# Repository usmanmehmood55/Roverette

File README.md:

# Roverette
A small robot or "rover" with some sensors, and WiFi.

Components included:
- [ESP32-WROOM32D](https://lcsc.com/product-detail/WIFI-Modules_Espressif-Systems-ESP32-WROOM-32_C82899.html) 
- [DRV8874](https://www.ti.com/lit/ds/symlink/drv8874.pdf)
- [TPS56628](https://www.ti.com/lit/ds/symlink/tps56628.pdf)
- There's more but I'll add those to the readme later

## To Do
- Complete IMU schematic
- Power path circuit for giving power to ESP32 via USB if connected
- Figure out what the motor placement should be
- PCB outline and component placement

View this project on [CADLAB.io](https://cadlab.io/project/23693), and on [GitHub](https://github.com/usmanmehmood55/Roverette).

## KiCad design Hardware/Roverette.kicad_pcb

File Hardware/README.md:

# Hardware
This folder will contain the KiCAD Project, Schematics & Layout and Project Libraries.

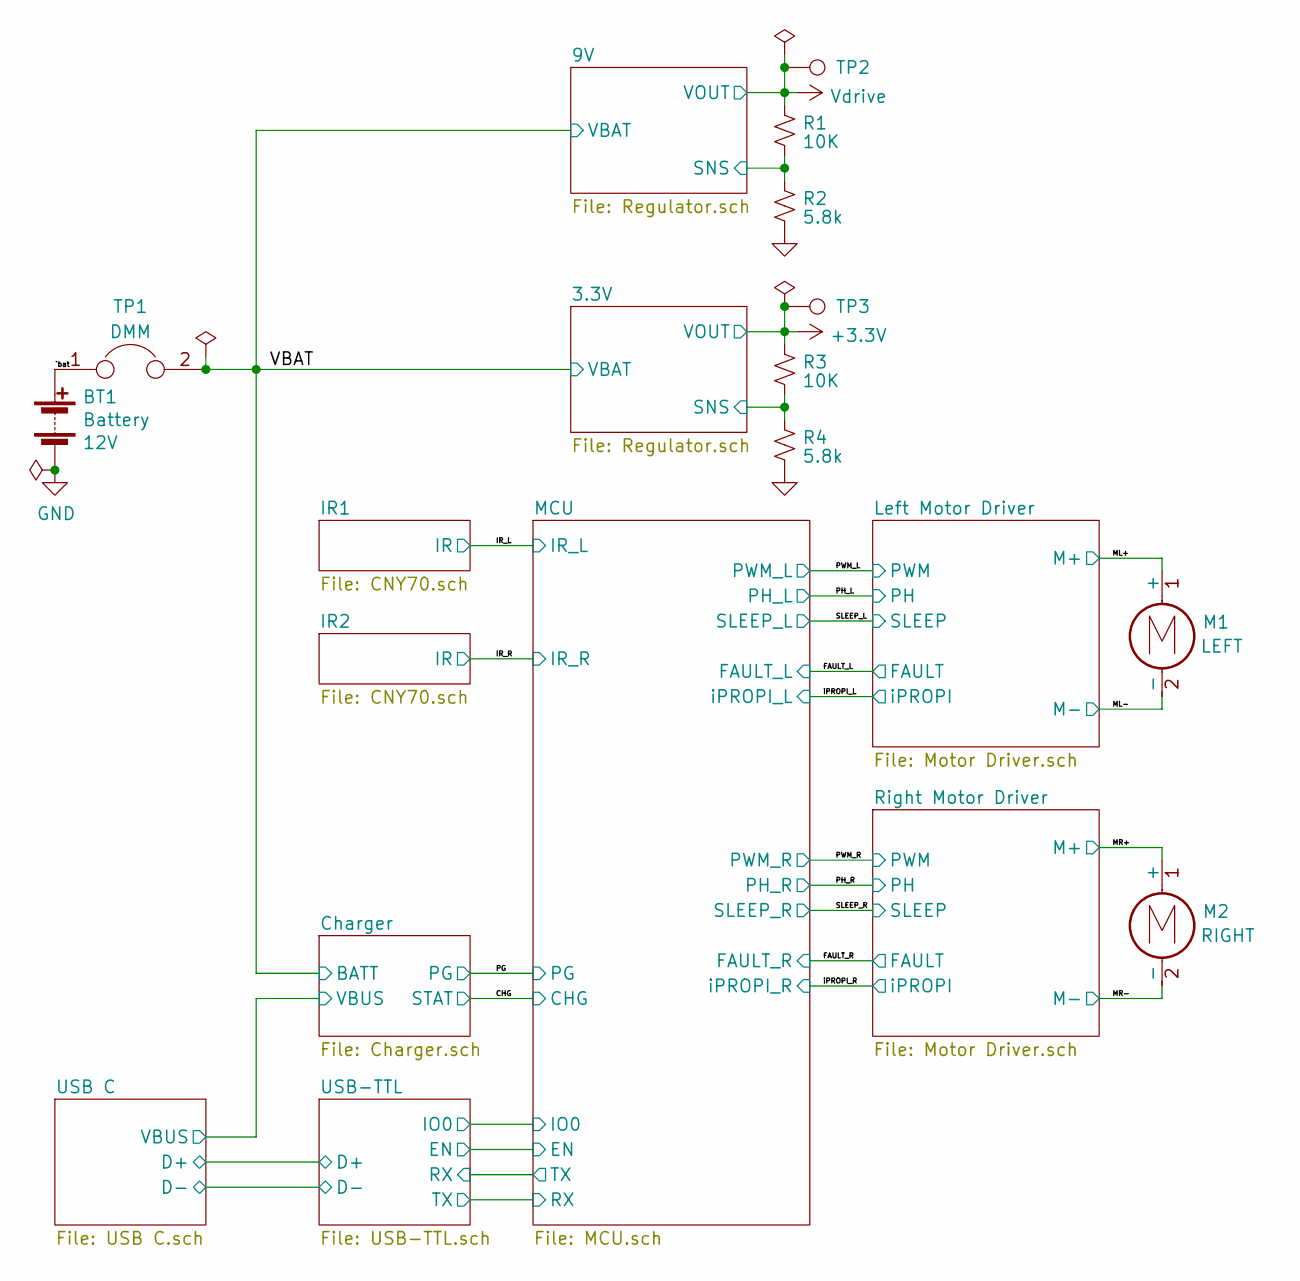
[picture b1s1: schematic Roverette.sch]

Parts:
BT1: Battery; TerminalBlock_bornier-2_P5.08mm
M1, M2: Motor_DC; TerminalBlock_bornier-2_P5.08mm
R1, R3: 10K; R_0805_2012Metric
R2, R4: 5.8k; R_0805_2012Metric
TP1: TestPoint_2Pole; TestPoint_2Pads_Pitch2.54mm_Drill0.8mm
TP2: vDrive; TestPoint_Loop_D1.80mm_Drill1.0mm_Beaded
TP3: 3v3; TestPoint_Loop_D1.80mm_Drill1.0mm_Beaded

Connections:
+3V3: R3.1, TP3.1; also elsewhere on the board
+BATT: TP1.2; also elsewhere on the board
/3.3V/SNS: R3.2, R4.1; also elsewhere on the board
/9V/SNS: R1.2, R2.1; also elsewhere on the board
/ML+: M1.1 (+); also elsewhere on the board
/ML-: M1.2 (-); also elsewhere on the board
/MR+: M2.1 (+); also elsewhere on the board
/MR-: M2.2 (-); also elsewhere on the board
/`bat: BT1.1 (+), TP1.1
GND: BT1.2 (-), R2.2, R4.2; also elsewhere on the board
Vdrive: R1.1, TP2.1; also elsewhere on the board

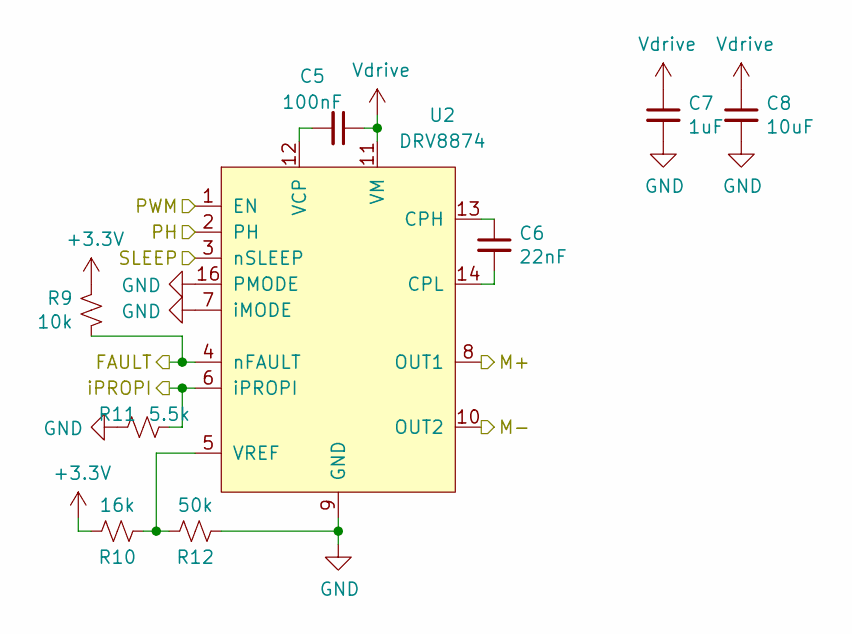
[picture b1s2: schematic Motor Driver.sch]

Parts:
C1: 100nF; C_0805_2012Metric
C2: 22nF; C_0805_2012Metric
C3: 1uF; C_0805_2012Metric
C4: 10uF; C_2220_5650Metric
R5: 10k; R_0805_2012Metric
R6: 16k; R_0805_2012Metric
R7: 5.5k; R_0805_2012Metric
R8: 50k; R_0805_2012Metric
U1: DRV8874; HTSSOP-16-1EP_4.4x5mm_P0.65mm_EP3.4x5mm_Mask3x3mm_ThermalVi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

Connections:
+3V3: R5.1, R6.2; also elsewhere on the board
/FAULT_L: R5.2, U1.4 (nFAULT); also elsewhere on the board
/ML+: U1.8 (OUT1); also elsewhere on the board
/ML-: U1.10 (OUT2); also elsewhere on the board
/PH_L: U1.2 (PH); also elsewhere on the board
/PWM_L: U1.1 (EN); also elsewhere on the board
/SLEEP_L: U1.3 (nSLEEP); also elsewhere on the board
/iPROPI_L: R7.1, U1.6 (iPROPI); also elsewhere on the board
GND: C3.2, C4.2, R7.2, R8.1, U1.7 (iMODE), U1.9 (GND), U1.15 (GND), U1.16 (PMODE), U1.17 (GND); also elsewhere on the board
unnamed: C1.2, U1.12 (VCP)
unnamed: C2.1, U1.13 (CPH)
unnamed: C2.2, U1.14 (CPL)
unnamed: R6.1, R8.2, U1.5 (VREF)
Vdrive: C1.1, C3.1, C4.1, U1.11 (VM); also elsewhere on the board

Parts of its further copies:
C5: 100nF; C_0805_2012Metric
C6: 22nF; C_0805_2012Metric
C7: 1uF; C_0805_2012Metric
C8: 10uF; C_2220_5650Metric
R9: 10k; R_0805_2012Metric
R10: 16k; R_0805_2012Metric
R11: 5.5k; R_0805_2012Metric
R12: 50k; R_0805_2012Metric
U2: DRV8874; HTSSOP-16-1EP_4.4x5mm_P0.65mm_EP3.4x5mm_Mask3x3mm_ThermalVi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

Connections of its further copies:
+3V3: R9.1, R10.2; also elsewhere on the board
/FAULT_R: R9.2, U2.4 (nFAULT); also elsewhere on the board
/MR+: U2.8 (OUT1); also elsewhere on the board
/MR-: U2.10 (OUT2); also elsewhere on the board
/PH_R: U2.2 (PH); also elsewhere on the board
/PWM_R: U2.1 (EN); also elsewhere on the board
/SLEEP_R: U2.3 (nSLEEP); also elsewhere on the board
/iPROPI_R: R11.1, U2.6 (iPROPI); also elsewhere on the board
GND: C7.2, C8.2, R11.2, R12.1, U2.7 (iMODE), U2.9 (GND), U2.15 (GND), U2.16 (PMODE), U2.17 (GND); also elsewhere on the board
unnamed: C5.2, U2.12 (VCP)
unnamed: C6.1, U2.13 (CPH)
unnamed: C6.2, U2.14 (CPL)
unnamed: R10.1, R12.2, U2.5 (VREF)
Vdrive: C5.1, C7.1, C8.1, U2.11 (VM); also elsewhere on the board

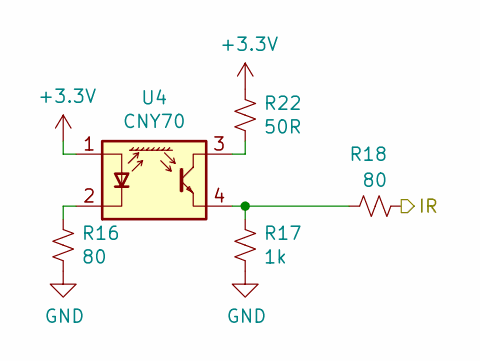
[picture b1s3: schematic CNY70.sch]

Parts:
R13, R15: 80; R_0805_2012Metric
R14: 1k; R_0805_2012Metric
R21: 50R; R_0805_2012Metric
U3: CNY70; Vishay_CNY70

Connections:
+3V3: R21.1, U3.1 (A); also elsewhere on the board
/IR_L: R15.2; also elsewhere on the board
GND: R13.2, R14.2; also elsewhere on the board
unnamed: R13.1, U3.2 (K)
unnamed: R14.1, R15.1, U3.4 (E)
unnamed: R21.2, U3.3 (C)

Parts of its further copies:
R16, R18: 80; R_0805_2012Metric
R17: 1k; R_0805_2012Metric
R22: 50R; R_0805_2012Metric
U4: CNY70; Vishay_CNY70

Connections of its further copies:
+3V3: R22.1, U4.1 (A); also elsewhere on the board
/IR_R: R18.2; also elsewhere on the board
GND: R16.2, R17.2; also elsewhere on the board
unnamed: R16.1, U4.2 (K)
unnamed: R17.1, R18.1, U4.4 (E)
unnamed: R22.2, U4.3 (C)

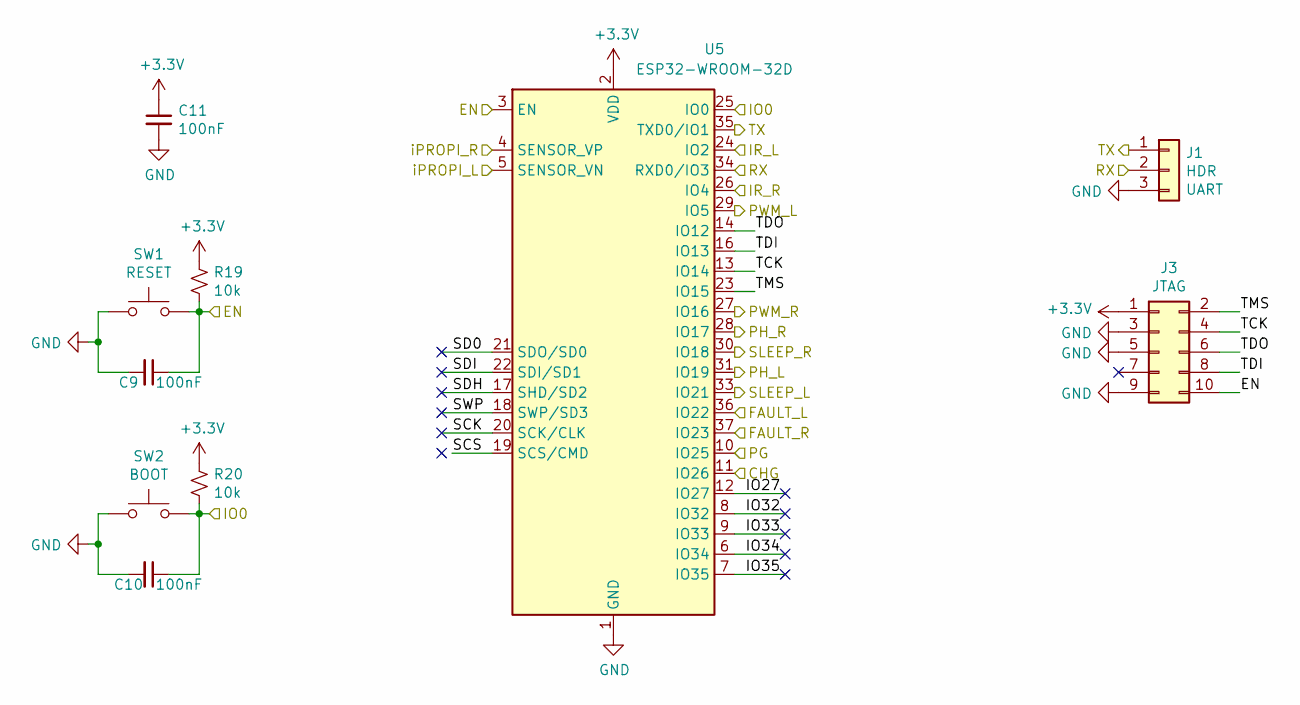
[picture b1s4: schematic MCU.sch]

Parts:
C9, C10, C11: 100nF; C_0805_2012Metric
J1: HDR; PinHeader_1x03_P2.54mm_Vertical
J3: JTAG; PinHeader_2x05_P1.27mm_Vertical_SMD
R19, R20: 10k; R_0805_2012Metric
SW1, SW2: SW_Push; SW_SPST_CK_RS282G05A3
U5: ESP32-WROOM-32D; ESP32-WROOM-32

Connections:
+3V3: C11.1, J3.1, R19.1, R20.1, U5.2 (VDD); also elsewhere on the board
/CHG: U5.11 (IO26); also elsewhere on the board
/FAULT_L: U5.36 (IO22); also elsewhere on the board
/FAULT_R: U5.37 (IO23); also elsewhere on the board
/IR_L: U5.24 (IO2); also elsewhere on the board
/IR_R: U5.26 (IO4); also elsewhere on the board
/MCU/EN: C9.1, J3.10, R19.2, SW1.2, U5.3 (EN); also elsewhere on the board
/MCU/IO0: C10.1, R20.2, SW2.2, U5.25 (IO0); also elsewhere on the board
/MCU/IO27: U5.12 (IO27)
/MCU/IO32: U5.8 (IO32)
/MCU/IO33: U5.9 (IO33)
/MCU/IO34: U5.6 (IO34)
/MCU/IO35: U5.7 (IO35)
/MCU/RX: J1.2, U5.34 (RXD0/IO3); also elsewhere on the board
/MCU/SCK: U5.20 (SCK/CLK)
/MCU/SCS: U5.19 (SCS/CMD)
/MCU/SD0: U5.21 (SDO/SD0)
/MCU/SDH: U5.17 (SHD/SD2)
/MCU/SDI: U5.22 (SDI/SD1)
/MCU/SWP: U5.18 (SWP/SD3)
/MCU/TCK: J3.4, U5.13 (IO14)
/MCU/TDI: J3.8, U5.16 (IO13)
/MCU/TDO: J3.6, U5.14 (IO12)
/MCU/TMS: J3.2, U5.23 (IO15)
/PG: U5.10 (IO25); also elsewhere on the board
/PH_L: U5.31 (IO19); also elsewhere on the board
/PH_R: U5.28 (IO17); also elsewhere on the board
/PWM_L: U5.29 (IO5); also elsewhere on the board
/PWM_R: U5.27 (IO16); also elsewhere on the board
/SLEEP_L: U5.33 (IO21); also elsewhere on the board
/SLEEP_R: U5.30 (IO18); also elsewhere on the board
/USB-TTL/RX: J1.1, U5.35 (TXD0/IO1); also elsewhere on the board
/iPROPI_L: U5.5 (SENSOR_VN); also elsewhere on the board
/iPROPI_R: U5.4 (SENSOR_VP); also elsewhere on the board
GND: C9.2, C10.2, C11.2, J1.3, J3.3, J3.5, J3.9, SW1.1, SW2.1, U5.1 (GND), U5.15 (GND), U5.38 (GND), U5.39 (GND); also elsewhere on the board

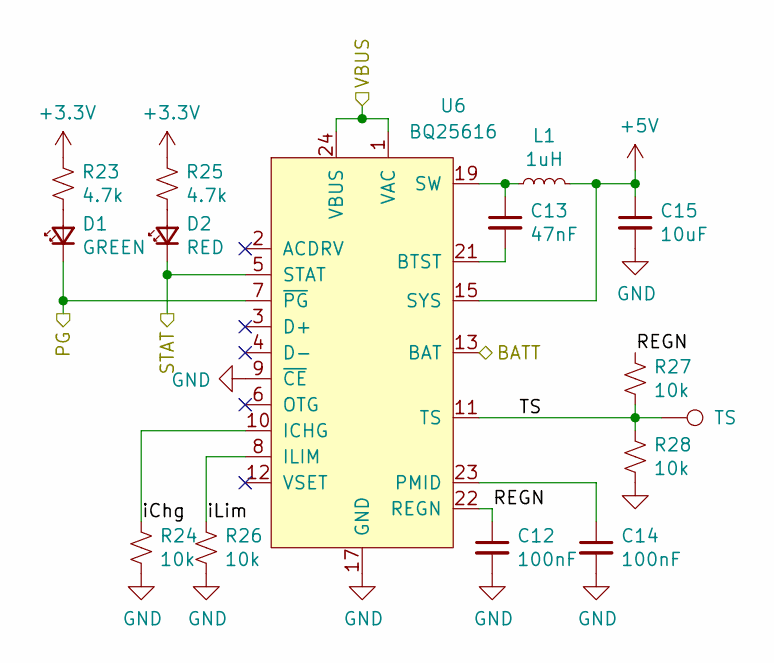
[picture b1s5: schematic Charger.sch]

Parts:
C12, C14: 100nF; C_0805_2012Metric
C13: 47nF; C_0805_2012Metric
C15: 10uF; C_0805_2012Metric
D1: GREEN; LED_0402_1005Metric
D2: RED; LED_0402_1005Metric
L1: 1uH; L_1210_3225Metric; MPN NLCV32T-1R0M-PF
R23, R25: 4.7k; R_0805_2012Metric
R24, R26, R27, R28: 10k; R_0805_2012Metric
TP4: TS; TestPoint_Pad_1.0x1.0mm
U6: BQ25616; WQFN-24-1EP_4x4mm_P0.5mm_EP2.6x2.6mm_ThermalVias

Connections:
+3V3: R23.1, R25.1; also elsewhere on the board
+5V: C15.1, L1.2, U6.15 (SYS), U6.16 (SYS)
+BATT: U6.13 (BAT), U6.14 (BAT); also elsewhere on the board
/CHG: D2.1 (K), U6.5 (STAT); also elsewhere on the board
/Charger/REGN: C12.1, R27.1, U6.22 (REGN)
/Charger/TS: R27.2, R28.1, TP4.1, U6.11 (TS)
/Charger/VBUS: U6.1 (VAC), U6.24 (VBUS); also elsewhere on the board
/Charger/iChg: R24.1, U6.10 (ICHG)
/Charger/iLim: R26.1, U6.8 (ILIM)
/PG: D1.1 (K), U6.7 (~PG); also elsewhere on the board
GND: C12.2, C14.2, C15.2, R24.2, R26.2, R28.2, U6.9 (~CE), U6.17 (GND), U6.18 (GND), U6.25 (GND); also elsewhere on the board
unnamed: C13.1, L1.1, U6.19 (SW), U6.20 (SW)
unnamed: C13.2, U6.21 (BTST)
unnamed: C14.1, U6.23 (PMID)
unnamed: D1.2 (A), R23.2
unnamed: D2.2 (A), R25.2

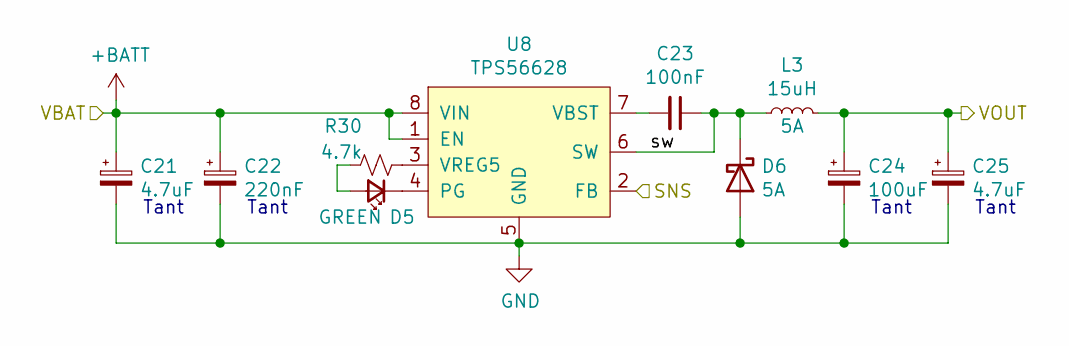
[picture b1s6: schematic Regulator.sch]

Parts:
C16, C20: 4.7uF; CP_EIA-3528-15_AVX-H
C17: 220nF; CP_EIA-3216-18_Kemet-A
C18: 100nF; C_0805_2012Metric
C19: 100uF; CP_EIA-7343-31_Kemet-D
D3: GREEN; LED_0805_2012Metric
D4: 5A; D_SOD-123F
L2: 15uH; L_Neosid_SMs42
R29: 4.7k; R_0805_2012Metric
U7: TPS56628; HSOP-8-1EP_3.9x4.9mm_P1.27mm_EP2.41x3.1mm_ThermalVias

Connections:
+3V3: C19.1, C20.1, L2.2; also elsewhere on the board
+BATT: C16.1, C17.1, U7.1 (EN), U7.8 (VIN); also elsewhere on the board
/3.3V/SNS: U7.2 (FB); also elsewhere on the board
/3.3V/sw: C18.1, D4.1 (K), L2.1, U7.6 (SW)
GND: C16.2, C17.2, C19.2, C20.2, D4.2 (A), U7.5 (GND), U7.9 (GND); also elsewhere on the board
unnamed: C18.2, U7.7 (VBST)
unnamed: D3.1 (K), U7.4 (PG)
unnamed: D3.2 (A), R29.1
unnamed: R29.2, U7.3 (VREG5)

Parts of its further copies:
C21, C25: 4.7uF; CP_EIA-3528-15_AVX-H
C22: 220nF; CP_EIA-3216-18_Kemet-A
C23: 100nF; C_0805_2012Metric
C24: 100uF; CP_EIA-7343-31_Kemet-D
D5: GREEN; LED_0805_2012Metric
D6: 5A; D_SOD-123F
L3: 15uH; L_Neosid_SMs42
R30: 4.7k; R_0805_2012Metric
U8: TPS56628; HSOP-8-1EP_3.9x4.9mm_P1.27mm_EP2.41x3.1mm_ThermalVias

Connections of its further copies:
+BATT: C21.1, C22.1, U8.1 (EN), U8.8 (VIN); also elsewhere on the board
/9V/SNS: U8.2 (FB); also elsewhere on the board
/9V/sw: C23.1, D6.1 (K), L3.1, U8.6 (SW)
GND: C21.2, C22.2, C24.2, C25.2, D6.2 (A), U8.5 (GND), U8.9 (GND); also elsewhere on the board
unnamed: C23.2, U8.7 (VBST)
unnamed: D5.1 (K), U8.4 (PG)
unnamed: D5.2 (A), R30.1
unnamed: R30.2, U8.3 (VREG5)
Vdrive: C24.1, C25.1, L3.2; also elsewhere on the board

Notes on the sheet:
Tant

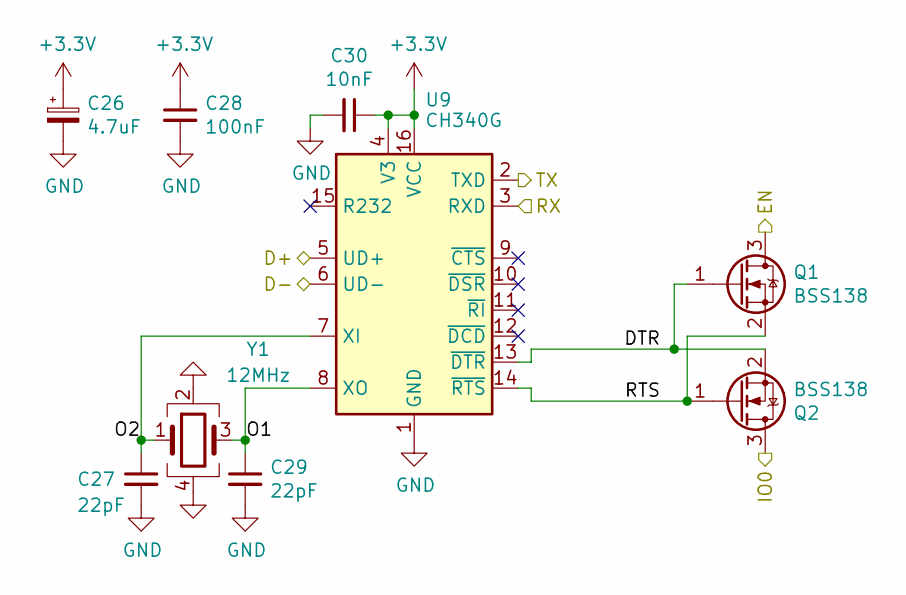
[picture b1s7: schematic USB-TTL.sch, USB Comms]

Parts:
C26: 4.7uF; CP_EIA-3528-15_AVX-H
C27, C29: 22pF; C_0805_2012Metric
C28: 100nF; C_0805_2012Metric
C30: 10nF; C_0805_2012Metric
Q1, Q2: BSS138; SOT-23
U9: CH340G; SOIC-16_3.9x9.9mm_P1.27mm
Y1: 12MHz; Crystal_SMD_3225-4Pin_3.2x2.5mm

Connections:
+3V3: C26.1, C28.1, C30.1, U9.4 (V3), U9.16 (VCC); also elsewhere on the board
/MCU/EN: Q1.3 (D); also elsewhere on the board
/MCU/IO0: Q2.3 (D); also elsewhere on the board
/MCU/RX: U9.2 (TXD); also elsewhere on the board
/USB C/D+: U9.5 (UD+); also elsewhere on the board
/USB C/D-: U9.6 (UD-); also elsewhere on the board
/USB-TTL/DTR: Q1.1 (G), Q2.2 (S), U9.13 (~DTR)
/USB-TTL/O1: C29.1, U9.8 (XO), Y1.3
/USB-TTL/O2: C27.1, U9.7 (XI), Y1.1
/USB-TTL/RTS: Q1.2 (S), Q2.1 (G), U9.14 (~RTS)
/USB-TTL/RX: U9.3 (RXD); also elsewhere on the board
GND: C26.2, C27.2, C28.2, C29.2, C30.2, U9.1 (GND), Y1.2, Y1.4; also elsewhere on the board

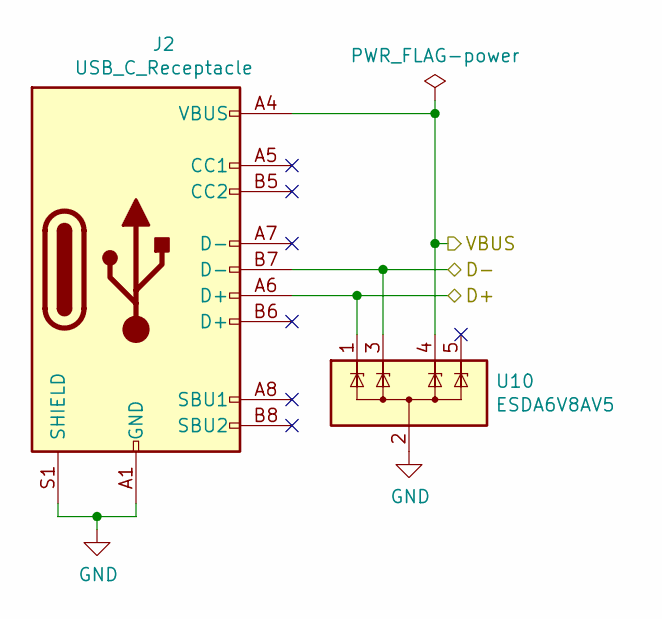
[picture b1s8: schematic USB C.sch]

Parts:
J2: USB_C_Receptacle; USB_C_Receptacle_XKB_U262-16XN-4BVC11
U10: ESDA6V8AV5; SOT-553

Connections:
/Charger/VBUS: J2.A4 (VBUS), J2.A9 (VBUS), J2.B4 (VBUS), J2.B9 (VBUS), U10.4; also elsewhere on the board
/USB C/D+: J2.A6 (D+), U10.1; also elsewhere on the board
/USB C/D-: J2.B7 (D-), U10.3; also elsewhere on the board
GND: J2.A1 (GND), J2.A12 (GND), J2.B1 (GND), J2.B12 (GND), J2.S1 (SHIELD), U10.2; also elsewhere on the board

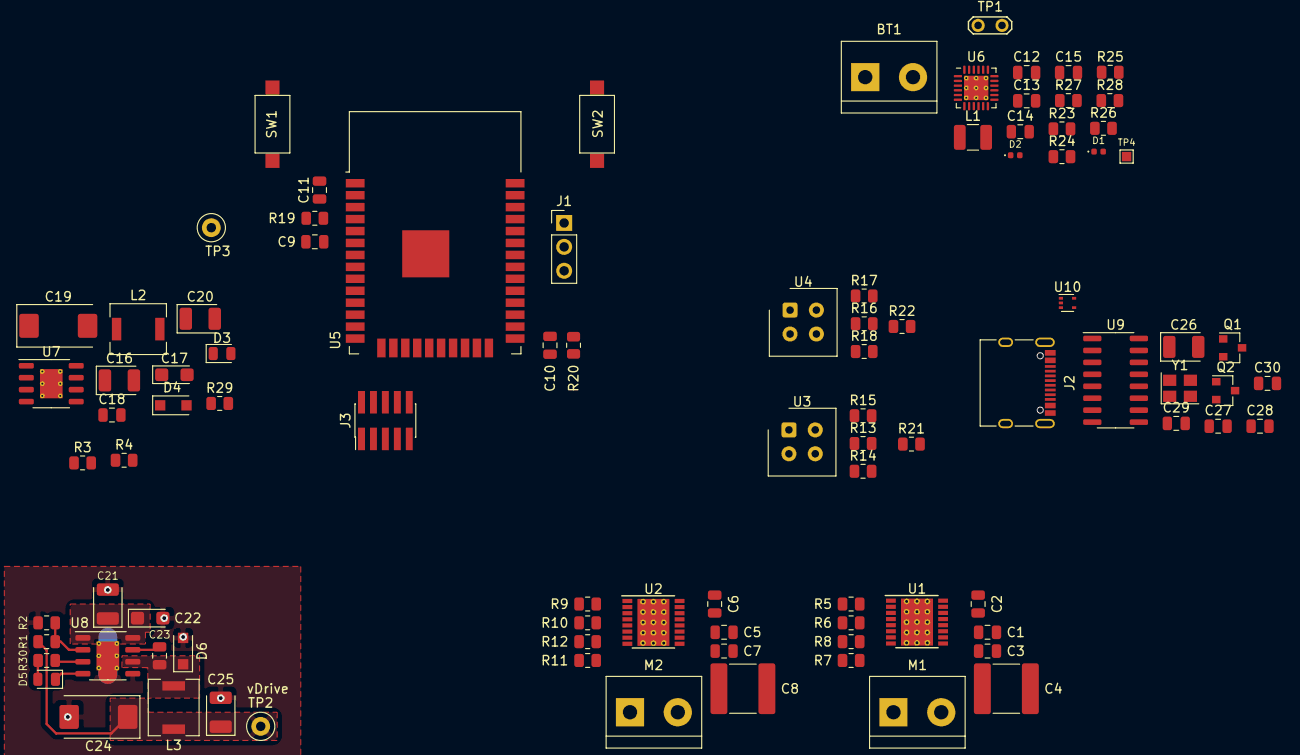
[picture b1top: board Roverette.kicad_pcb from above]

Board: 2 copper layers, 94 parts (0 on the bottom side), 74 nets.

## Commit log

2020-10-23 test
2020-12-30 Tidying up
2020-12-30 Readme updated
2020-12-30 Added firmware folder structure
2020-12-31 Test pads changed to push buttons, DMM test point added for measuring current Signed-off-by: Usman <usmanmehmood55@gmail.com>
2020-12-31 Added footprint
2020-12-31 Schematic updated
2020-12-31 Signature test
2020-12-31 Schematic divided into sub-sheets
2020-12-31 Testing CADLab Signed-off-by: Usman <usmanmehmood55@gmail.com>
2020-12-31 CADLab test
2020-12-31 CADLAB integration complete
2020-12-31 Motor driver and power management subsheet converted to blocks
2020-12-31 old motor driver schematic removed
2020-12-31 schematic fixed
2020-12-31 readme
2021-01-01 Schematic and readme updated
2021-01-01 Battery charger IC added
2021-01-01 Net names declared in root sheet
2021-01-20 Replaced ESP-WROOM-32D with ESP32-CAM
2021-04-21 Schematic updated, USB comms circuit added
2021-04-26 vbus connected from USB to charger sheet
2022-09-04 PCB design started
2022-09-08 Did placements and routing of one regulator
